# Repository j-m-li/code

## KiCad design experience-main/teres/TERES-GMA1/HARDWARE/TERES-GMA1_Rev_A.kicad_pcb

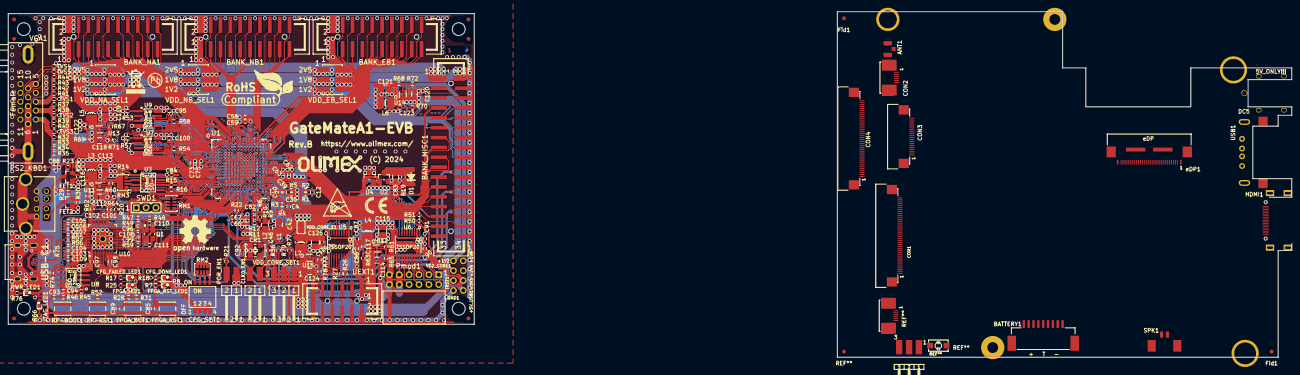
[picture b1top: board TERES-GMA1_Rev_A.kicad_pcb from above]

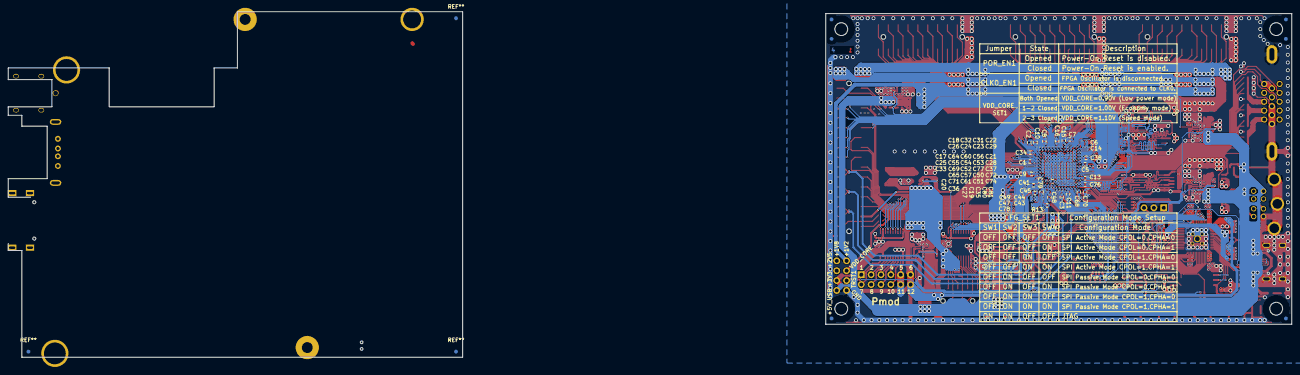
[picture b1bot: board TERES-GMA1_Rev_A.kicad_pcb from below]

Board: 4 copper layers, 120.0 x 80.0 mm, 318 parts (73 on the bottom side), 264 nets.

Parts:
+1V2, +1V8, +2V5, +3V3, +5V_USB1: TESTPAD; TEST_PAD_40x70_Round
ANT1: PCB_WIFI_ANT; U.FL-R-SMT-1
BANK_EB1: B-V-20-LF; GBH-254-SMT-20
BANK_MISC1: B-V-34-LF; GBH-254-SMT-34
BANK_NA1: B-V-20-LF; GBH-254-SMT-20
BANK_NB1: B-V-20-LF; GBH-254-SMT-20
BATTERY1: BATTCON; BATCONN-TERES
C1, C2, C3, C4, C5, C6, C7, C8, C43, C47, C58, C62, C66, C68, C73, C78, C106, C107: 2.2uF/6.3V/20%/X5R/C0402; C_0402_5MIL_DWS
C9, C10, C11, C12, C13, C14, C15, C16, C30, C42, C44, C46, C48, C59, C63, C67, C70, C75, C82, C85, C86, C87, C88, C89, C90, C91, C92, C94, C95, C96, C97, C98, C99, C100, C101, C102, C103, C104, C105, C108, C109: 100nF/10V/20%/X5R/C0402; C_0402_5MIL_DWS
C17, C18, C19, C20, C21, C22, C23, C24, C25, C26, C27, C28, C29, C31, C32, C33, C34, C35, C36, C37, C38, C41, C45, C49, C50, C51, C52, C53, C54, C55, C56, C57, C60, C61, C64, C65, C69, C71, C72, C74, C76, C77, C79, C80, C81: 1nF/50V/10%/X7R/C0402; C_0402_5MIL_DWS
C39, C40, C126: 10uF/6.3V/X5R/20%/C0402; C_0402_5MIL_DWS
C83, C112, C114, C118, C120, C124: 22uF/6.3V/20%/X5R/C0603; C_0603_5MIL_DWS
C84: NA(100nF/10V/20%/X5R/C0402); C_0402_5MIL_DWS
C93: NA/C0402; C_0402_5MIL_DWS
C110, C111: 18pF/50V/5%/C0G/C0402; C_0402_5MIL_DWS
C113, C115, C119, C121, C125: 47uF/6.3V/20%/X5R/C0805; C_0805_5MIL_DWS
C116, C117, C122, C123: NA(2.2uF/6.3V/20%/X5R/C0402); C_0402_5MIL_DWS
CFG_DONE_LED1: LED/GREEN/0603; LED_0603_KA
CFG_FAILED_LED1: LED/RED/0603; LED_0603_KA
CFG_SET1: DSHP04TS-S; DSHP04TS-S-1.27mm_Half_4_Slide
CLK0_EN1: H-WX-1x2-LF(Closed); HN1x2(SMD)_H-WX-1x2-LF
CON1, CON4: CONN_01X40; FPV-WZA21-40-LF
CON2: CONN_01X06; FLEXCON-0.5-6
CON3: CONN_01X20; FPV-WZA21-20-LF
CR1: Q10MHz/30ppm/1.62V-3.63V/4P/5x3.2mm(SX5M10.000M20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; 5032-4P_HCX-3S
D1: 1N5819S4/SOD123; SOD-123_1C-2A_KA
DC5: PWR-JACK-THERES; DC-055-TERES
FET1, FET2: BSS138(SOT-23-3); SOT23
FID1, FID2, FID3, FID7, FID8, FID9: Fiducial; Fiducial1x3
FID4, FID5, FID6, FID10, FID11, FID12: Fiducial; Fiducial1x3_Paste
FPGA_BUT1: YTS-A016-X
FPGA_LED1: LED/GREEN/0603; LED_0603_KA
FPGA_RST1: YTS-A016-X
FPGA_RST_LED1: LED/RED/0603; LED_0603_KA
Fid1, Fid1#2: Fiducial1x3_transp
GND1: TESTPAD; TEST_PAD_40x70_Round
HDMI1: HDMI-SWM-19; HDMI-MINI-TERES
JTAG_LED1: LED/YELLOW/0603; LED_0603_KA
JUMP_CAP1, JUMP_CAP2, JUMP_CAP3, JUMP_CAP4, JUMP_CAP5, JUMP_CAP6: MJ6
L1, L2: FB0805/600R/2A; L_0805_5MIL_DWS
L3, L4, L5, L6, L7: 1.0uH/2.5A/DCR=30mR/20%/3.00x3.00x1.50mm/CD32(SWP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; CD32
Logo_OLIMEX_TB: Logo_OLIMEX_TB
MH1, MH2, MH3, MH4: Mounting_Hole_NPTH; Mounting_Hole_Drill-3.3mm_Clerance-7mm
POR_EN1: H-WX-1x2-LF(Closed); HN1x2(SMD)_H-WX-1x2-LF
PS2_KBD1: MDR6_MINI-DIN; PS2_MDR6_MINI-DIN
PWR_LED1: LED/RED/0603; LED_0603_KA
Pmod1: F-R-2x06-LF; Digilent_Pmod_12-pin
Q1: Q12MHz/20pF/10ppm/4P/3.2x2.5mm; TSX-3.2x2.5mm_GND(3)
R1, R4: NA(200R/1%/R0402); R_0402_5MIL_DWS
R2, R3, R6, R10: 0R/R0402; R_0402_5MIL_DWS
R5: 4.7R/R0402; R_0402_5MIL_DWS
R7, R17, R18, R25, R26, R27, R66, R76: 2.2k/R0402; R_0402_5MIL_DWS
R8, R19, R23, R24, R28, R29, R30, R45, R53, R57: 10k/R0402; R_0402_5MIL_DWS
R9: NA(0R/R0402); R_0402_5MIL_DWS
R11, R12, R13, R15: NA(R0402); R_0402_5MIL_DWS
R14, R16, R21, R49: NA(10k/R0402); R_0402_5MIL_DWS
R20, R36, R46, R50, R51, R59: 100R/R0402; R_0402_5MIL_DWS
R22: 200R/1%/R0402; R_0402_5MIL_DWS
R31, R54, R58: 22R/R0402; R_0402_5MIL_DWS
R32, R37, R41: 430R/1%/R0402; R_0402_5MIL_DWS
R33, R38, R42: 866R/1%/R0402; R_0402_5MIL_DWS
R34, R39, R43: 2.05k/1%/R0402; R_0402_5MIL_DWS
R35, R40, R44: 4.42k/1%/R0402; R_0402_5MIL_DWS
R47, R48: NA(22R/R0402); R_0402_5MIL_DWS
R52: NA(100R/R0402); R_0402_5MIL_DWS
R55, R56: 27R/R0402; R_0402_5MIL_DWS
R60: 3.32k/1%/R0402; R_0402_5MIL_DWS
R61: 4.7k/1%/R0402; R_0402_5MIL_DWS
R62, R63, R69, R70: 100k/R0402; R_0402_5MIL_DWS
R64, R65: 1.05k/1%/R0402; R_0402_5MIL_DWS
R67: 20k/1%/R0402; R_0402_5MIL_DWS
R68, R71, R72: 10k/1%/R0402; R_0402_5MIL_DWS
R73: 1k/1%/R0402; R_0402_5MIL_DWS
R74, R75: 5.1k/1%/R0402; R_0402_5MIL_DWS
R77: 6.04k/1%/R0402; R_0402_5MIL_DWS
R78: 2k/1%/R0402; R_0402_5MIL_DWS
R79: 3.01k/1%/R0402; R_0402_5MIL_DWS
RM1, RM2: RA1206_(4x0603)_4B8_10k; RA1206_(4X0603)_4B8_xx
RM3: NA(RA1206_(4x0603)_4B8_10k); RA1206_(4X0603)_4B8_xx
RP-BOOT1: YTS-A016-X
RP-RST1: YTS-A016-X
SPK1: SPK1; CON-SPK-TERES
SWD1: NA(HN1x3); HN1x3
Sign_Antistatic: Sign_Antistatic
Sign_CE: CE_Sign
Sign_OSHW_8x8: Sign_OSHW_8x8
Sign_PB-Free: Sign_PB-Free
Sign_RecycleBin_1: Sign_RecycleBin_1
Sign_RoHS_1: Sign_RoHS_1
TRST1: TESTPAD; TEST_PAD_40x70_Round
TVS1, TVS2, TVS3, TVS4, TVS5: NA(GG0402052R542P); D_0402_5MIL_DWS
U1: CCGM1A1(FBGA-324); FBGA-324_P0.8mm_Pad0.4mm_Ball0.45mm_Dim15.00x15.00x1.20mm
U2: HX7027(SOT-23-3); SOT-23
U3: NA(ZD25WQ16CSIGT(SOIC-8_208mils)); SO-8_208mil
U4: NA(MCP120T-300I/TT(SOT-23-3)); SOT-23
U5, U6: TXB0108PWR(TSSOP-20); TSSOP20_Pitch-0.65mm_6.6x4.5x1.2mm
U7, U9: LY68S3200SLT(SOIC-8_150mil); SOIC-8_150mil
U8: ZD25WQ16CSIGT(SOIC-8_208mils); SO-8_208mil
U10: RP2040(QFN-56_7x7mm_P0.4mm); QFN56_7x7_Pitch_0.4mm
U11, U12, U13, U14, U15: TPS62A02ADRLR(SOT-563-6); SOT-563-6
UEXT1: P-B-V-10-LF; GBH-254-SMT-10
USB1: USB_A_THERES; USB-A-TERES
USB-C1: USB-C-16P-F(A40-00119-A52-12); USB2.0_TYPE-C(A40-00119-A52-12)_Paste
VDD_CORE1: TESTPAD; TEST_PAD_40x70_Round
VDD_CORE_E1: Closed; SJ_Closed
VDD_CORE_SET1: H-WX-1x3-LF(1-2:Closed/2-3:Opened); HN1x3(SMD)_H-WX-1x3-LF
VDD_EB_SEL1: H-V33X-2x03-LF(1-2:Closed); GPH254SMT02x03(H-V33X-2X3-LF)
VDD_NA_SEL1: H-V33X-2x03-LF(1-2:Closed); GPH254SMT02x03(H-V33X-2X3-LF)
VDD_NB_SEL1: H-V33X-2x03-LF(1-2:Closed); GPH254SMT02x03(H-V33X-2X3-LF)
VGA1: HDR15-3.08-14.5T/VGA15/14.5mm; VGA15-F(HDR15-3.08-14.5T)_DrillSlot
eDP1: LCD_CONN; eDP-TERES

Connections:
+1V2: +1V2.1 (Pad), C121.1, L6.2, R68.2, VDD_EB_SEL1.5, VDD_NA_SEL1.5, VDD_NB_SEL1.5
+1V8: +1V8.1 (Pad), BANK_MISC1.2, C6.1, C14.1, C22.2, C29.2, C38.2, C95.2, C100.2, C119.1, L5.2, R53.1, R57.1, R67.2, U1.A2 (VDD_WC), U1.C2 (VDD_WC), U1.D5 (VDD_WC), U1.F2 (VDD_WC), U1.F5 (VDD_WC), U7.8 (VCC), U9.8 (VCC), VDD_EB_SEL1.3, VDD_NA_SEL1.3, VDD_NB_SEL1.3
+2V5: +2V5.1 (Pad), BANK_MISC1.1, C1.2, C3.2, C4.1, C5.2, C9.1, C11.1, C12.1, C13.1, C17.1, C19.1, C20.2, C21.1, C25.1, C27.1, C28.1, C33.1, C35.1, C36.2, C37.1, C68.1, C70.1, C72.1, C74.1, C76.1, C78.2, C79.1, C80.1, C81.1, C84.2, C87.1, C91.1, C92.2, C94.2, C97.1, C98.1, C99.1, C101.1, C102.1, C103.1, C106.1, C113.1, CFG_FAILED_LED1.2 (A), CFG_SET1.1 (SW1_A), CFG_SET1.2 (SW2_A), CFG_SET1.3 (SW3_A), CFG_SET1.4 (SW4_A), CR1.1 (E/D), CR1.4 (VDD), FET1.1 (G), FET2.1 (G), FPGA_LED1.2 (A), FPGA_RST_LED1.2 (A), L3.2, POR_EN1.1, R2.1, R3.1, R8.2, R11.2, R14.2, R15.2, R24.1, R28.2, R30.1, R45.1, R49.1, R60.2, RM1.1.2, RM1.2.2, RM1.3.2, RM3.1.2, RM3.2.2, RM3.3.2, RM3.4.2, U1.G14 (VDD_EA), U1.H5 (VDD_WB), U1.H17 (VDD_EA), U1.J2 (VDD_WB), U1.J14 (VDD_EA), U1.K5 (VDD_WB), U1.L14 (VDD_EA), U1.L17 (VDD_EA), U1.M2 (VDD_WB), U1.M5 (VDD_WB), U1.N5 (VDD_WA), U1.N11 (VDD_SB), U1.N13 (VDD_SB), U1.P3 (VDD_WA), U1.P5 (VDD_WA), U1.P6 (VDD_SA), U1.P8 (VDD_SA), U1.P10 (VDD_SA), U1.R15 (VDD_SB), U1.T1 (VDD_WA), U1.T14 (VDD_CLK), U1.U3 (VDD_WA), U1.U6 (VDD_SA), U1.U9 (VDD_SA), U3.8 (VCC), U5.2 (Vcca), U5.10 (OE), U6.2 (Vcca), U6.10 (OE), U8.8 (VCC), U10.1 (IOVDD), U10.10 (IOVDD), U10.22 (IOVDD), U10.33 (IOVDD), U10.42 (IOVDD), U10.44 (VREG_VIN), U10.49 (IOVDD), VDD_EB_SEL1.1, VDD_NA_SEL1.1, VDD_NB_SEL1.1
+3V3: +3V3.1 (Pad), C86.1, C90.1, C104.1, C105.1, C115.1, D1.1 (K), L4.2, Pmod1.6, Pmod1.12, R19.1, R26.1, R27.1, R61.2, U4.2 (VDD), U5.19 (Vccb), U6.19 (Vccb), U10.43 (ADC_AVDD), U10.48 (USB_VDD), UEXT1.1
+5V_USB: +5V_USB1.1 (Pad), C88.1, C112.1, C114.1, C118.1, C120.1, C124.1, PS2_KBD1.4, PWR_LED1.2 (A), R23.1, R29.1, R62.2, R63.2, R69.2, R70.2, U11.3 (VIN), U12.3 (VIN), U13.3 (VIN), U14.3 (VIN), U15.3 (VIN), U15.4 (EN), USB-C1.A4 (VBUS), USB-C1.A9 (VBUS), USB-C1.B4 (VBUS), USB-C1.B9 (VBUS)
/+1V1: C107.1, C108.1, C109.1, U10.23 (DVDD), U10.45 (VREG_VOUT), U10.50 (DVDD)
/CFG_DONE: CFG_DONE_LED1.2 (A), U1.V3 (IO_WA_B2/CFG_DONE)
/CFG_MD0: CFG_SET1.5 (SW4_B), RM2.4.1, U1.R5 (CFG_MD0/IO_WA_A0)
/CFG_MD1: CFG_SET1.6 (SW3_B), RM2.3.1, U1.T5 (CFG_MD1/IO_WA_B0)
/CFG_MD2: CFG_SET1.7 (SW2_B), RM2.2.1, U1.U4 (CFG_MD2/IO_WA_A1)
/CFG_MD3: CFG_SET1.8 (SW1_B), RM2.1.1, U1.V4 (CFG_MD3/IO_WA_B1)
/CLK: U8.6 (CLK), U10.52 (QSPI_SCLK(Soft_GPIO))
/CLK0: CLK0_EN1.1, R50.1, U1.N14 (CLK0/IO_SB_A8)
/CLK3: R51.2, U1.R13 (CLK3/IO_SB_A5)
/CSn: C93.2, R45.2, R46.1, U8.1 (#CS), U10.56 (QSPI_SS_N(Soft_GPIO))
/D+: R56.2, U10.47 (USB_DP)
/D-: R55.2, U10.46 (USB_DM)
/EA_A0: U1.M15 (IO_EA_A0), U5.1 (A1)
/EA_A1: U1.L16 (IO_EA_A1), U5.4 (A3)
/EA_A2: U1.K18 (IO_EA_A2), U5.6 (A5)
/EA_A3: U1.K16 (IO_EA_A3), U5.8 (A7)
/EA_A4: U1.J18 (IO_EA_A4), U6.1 (A1)
/EA_A5: U1.J16 (IO_EA_A5), U6.4 (A3)
/EA_A6: U1.H16 (IO_EA_A6), U6.6 (A5)
/EA_A7: U1.G18 (IO_EA_A7), U6.8 (A7)
/EA_A8: BANK_MISC1.5, U1.G16 (IO_EA_A8)
/EA_B0: U1.M14 (IO_EA_B0), U5.3 (A2)
/EA_B1: U1.L15 (IO_EA_B1), U5.5 (A4)
/EA_B2: U1.K17 (IO_EA_B2), U5.7 (A6)
/EA_B3: U1.K15 (IO_EA_B3), U5.9 (A8)
/EA_B4: U1.J17 (IO_EA_B4), U6.3 (A2)
/EA_B5: U1.J15 (IO_EA_B5), U6.5 (A4)
/EA_B6: U1.H15 (IO_EA_B6), U6.7 (A6)
/EA_B7: U1.G17 (IO_EA_B7), U6.9 (A8)
/EA_B8: BANK_MISC1.7, U1.G15 (IO_EA_B8)
/EB_A0: BANK_EB1.19, U1.F18 (IO_EB_A0)
/EB_A1: BANK_EB1.17, U1.F16 (IO_EB_A1)
/EB_A2: BANK_EB1.15, U1.D18 (IO_EB_A2)
/EB_A3: BANK_EB1.13, U1.E16 (IO_EB_A3)
/EB_A4: BANK_EB1.11, U1.C18 (IO_EB_A4)
/EB_A5: BANK_EB1.9, U1.B17 (IO_EB_A5)
/EB_A6: BANK_EB1.7, U1.D16 (IO_EB_A6)
/EB_A7: BANK_EB1.5, U1.D15 (IO_EB_A7)
/EB_A8: BANK_EB1.3, U1.B15 (IO_EB_A8)
/EB_B0: BANK_EB1.20, U1.F17 (IO_EB_B0)
/EB_B1: BANK_EB1.18, U1.F15 (IO_EB_B1)
/EB_B2: BANK_EB1.16, U1.D17 (IO_EB_B2)
/EB_B3: BANK_EB1.14, U1.E15 (IO_EB_B3)
/EB_B4: BANK_EB1.12, U1.C17 (IO_EB_B4)
/EB_B5: BANK_EB1.10, U1.A17 (IO_EB_B5)
/EB_B6: BANK_EB1.8, U1.C16 (IO_EB_B6)
/EB_B7: BANK_EB1.6, U1.C15 (IO_EB_B7)
/EB_B8: BANK_EB1.4, U1.A15 (IO_EB_B8)
/FPGA_BUT: R31.2, U1.P13 (IO_SB_B7)
/FPGA_LED: R25.2, U1.P15 (IO_SB_B6)
/FPGA_RESET_IN: BANK_MISC1.29, C85.2, FPGA_RST1.1, R7.2, R8.1, R20.1, R52.2, U1.T15 (RST_N), U2.1 (VOut), U4.1 (#RST)
/FPGA_SPI_CLK: R15.1, R16.1, U1.N4 (IO_WA_B8/SPI_CLK), U3.6 (CLK)
/FPGA_SPI_CSN: R14.1, U1.N3 (IO_WA_A8/~SPI_CS), U3.1 (#CS)
/FPGA_SPI_D0: RM3.1.1, U1.P2 (IO_WA_B7/SPI_D0), U3.5 (DI(IO0))
/FPGA_SPI_D1: RM3.3.1, U1.P1 (IO_WA_A7/SPI_D1), U3.2 (DO(IO1))
/FPGA_SPI_D2: RM3.2.1, U1.R2 (IO_WA_B6/SPI_D2), U3.3 (#WP(IO2))
/FPGA_SPI_D3: RM3.4.1, U1.R1 (IO_WA_A6/SPI_D3), U3.7 (#HOLD(IO3))
/FPGA_SPI_FWD: BANK_MISC1.3, U1.R4 (IO_WA_B5/SPI_FWD)
/GPIO0: U1.U5 (IO_SA_A0), U10.2 (GPIO0/SPI0_RX/UART0_TX/I2C0_SDA/PWM0_A/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)
/GPIO1: U1.V5 (IO_SA_B0), U10.3 (GPIO1/SPI0_CSn/UART0_RX/I2C0_SCL/PWM0_B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)
/GPIO2: U1.R6 (IO_SA_A1), U10.4 (GPIO2/SPI0_SCK/UART0_CTS/I2C1_SDA/PWM1_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)
/GPIO3: U1.T6 (IO_SA_B1), U10.5 (GPIO3/SPI0_TX/UART0_RTS/I2C1_SCL/PWM1_B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)
/GPIO4: U1.R7 (IO_SA_A2), U10.6 (GPIO4/SPI0_RX/UART1_TX/I2C0_SDA/PWM2_A/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)
/GPIO5: U1.T7 (IO_SA_B2), U10.7 (GPIO5/SPI0_CSn/UART1_RX/I2C0_SCL/PWM2_B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)
/GPIO6: U1.U7 (IO_SA_A3), U10.8 (GPIO6/SPI0_SCK/UART1_CTS/I2C1_SDA/PWM3_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)
/GPIO7: U1.V7 (IO_SA_B3), U10.9 (GPIO7/SPI0_TX/UART1_RTS/I2C1_SCL/PWM3_B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)
/GPIO8: U1.R8 (IO_SA_A4), U10.11 (GPIO8/SPI1_RX/UART1_TX/I2C0_SDA/PWM4_A/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)
/GPIO9: U1.T8 (IO_SA_B4), U10.12 (GPIO9/SPI1_CSn/UART1_RX/I2C0_SCL/PWM4_B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)
/GPIO10: U1.U8 (IO_SA_A5), U10.13 (GPIO10/SPI1_SCK/UART1_CTS/I2C1_SDA/PWM5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)
/GPIO11: U1.V8 (IO_SA_B5), U10.14 (GPIO11/SPI1_TX/UART1_RTS/I2C1_SCL/PWM5_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)
/GPIO12\DBG-UART_TX: U1.R9 (IO_SA_A6), U10.15 (GPIO12/SPI1_RX/UART0_TX/I2C0_SDA/PWM6_A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)
/GPIO13\DBG-UART_RX: U1.T9 (IO_SA_B6), U10.16 (GPIO13/SPI1_CSn/UART0_RX/I2C0_SCL/PWM6_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)
/GPIO14: U1.R10 (IO_SA_A7), U10.17 (GPIO14/SPI1_SCK/UART0_CTS/I2C1_SDA/PWM7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)
/GPIO15: U1.T10 (IO_SA_B7), U10.18 (GPIO15/SPI1_TX/UART0_RTS/I2C1_SCL/PWM7_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)
/GPIO16\JTAG_TDI: RM1.3.1, U1.T2 (JTAG_TDI/IO_WA_A4), U10.27 (GPIO16/SPI0_RX/UART0_TX/I2C0_SDA/PWM0_A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)
/GPIO17\JTAG_TDO: RM1.2.1, U1.U2 (JTAG_TDO/IO_WA_B3), U10.28 (GPIO17/SPI0_CSn/UART0_RX/I2C0_SCL/PWM0_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)
/GPIO18\JTAG_TCK: RM1.4.1, U1.R3 (JTAG_TCK/IO_WA_A5), U10.29 (GPIO18/SPI0_SCK/UART0_CTS/I2C1_SDA/PWM1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)
/GPIO19\JTAG_TMS: RM1.1.1, U1.T3 (JTAG_TMS/IO_WA_B4), U10.30 (GPIO19/SPI0_TX/UART0_RTS/I2C1_SCL/PWM1_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)
/GPIO20\JTAG_RST: R20.2, U10.31 (GPIO20/SPI0_RX/UART1_TX/I2C0_SDA/PWM2_A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)
/GPIO21\JTAG_TRST: TRST1.1 (Pad), U10.32 (GPIO21/SPI0_CSn/UART1_RX/I2C0_SCL/PWM2_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)
/GPIO22\GPIN1: U1.N15 (IO_SB_B8), U10.34 (GPIO22/SPI0_SCK/UART1_CTS/I2C1_SDA/PWM3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)
/GPIO23\CLK1: U1.P12 (CLK1/IO_SB_A7), U10.35 (GPIO23/SPI0_TX/UART1_RTS/I2C1_SCL/PWM3_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)
/GPIO24\CLK2: U1.P14 (CLK2/IO_SB_A6), U10.36 (GPIO24/SPI1_RX/UART1_TX/I2C0_SDA/PWM4_A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)
/GPIO25\JTAG_LED: JTAG_LED1.2 (A), U1.R14 (IO_SB_B5), U10.37 (GPIO25/SPI1_CSn/UART1_RX/I2C0_SCL/PWM4_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)
/GPIO26: U1.R11 (IO_SB_B4), U10.38 (GPIO26/ADC0/SPI1_SCK/UART1_CTS/I2C1_SDA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)
/GPIO27: U1.P11 (IO_SB_A4), U10.39 (GPIO27/ADC1/SPI1_TX/UART1_RTS/I2C1_SCL/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)
/GPIO28: U1.U10 (IO_SA_A8), U10.40 (GPIO28/ADC2/SPI1_RX/UART0_TX/I2C0_SDA/P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)
/GPIO29: U1.V10 (IO_SA_B8), U10.41 (GPIO29/ADC3/SPI1_CSn/UART0_RX/I2C0_SCL/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)
/IO0: U8.5 (DI(IO0)), U10.53 (QSPI_SD0(Soft_GPIO))
/IO1: U8.2 (DO(IO1)), U10.55 (QSPI_SD1(Soft_GPIO))
/IO2: U8.3 (#WP(IO2)), U10.54 (QSPI_SD2(Soft_GPIO))
/IO3: U8.7 (#HOLD(IO3)), U10.51 (QSPI_SD3(Soft_GPIO))
/NA_A0: BANK_NA1.3, U1.A3 (IO_NA_A0)
/NA_A1: BANK_NA1.5, U1.A4 (IO_NA_A1)
/NA_A2: BANK_NA1.7, U1.B5 (IO_NA_A2)
/NA_A3: BANK_NA1.9, U1.C6 (IO_NA_A3)
/NA_A4: BANK_NA1.11, U1.A6 (IO_NA_A4)
/NA_A5: BANK_NA1.13, U1.C7 (IO_NA_A5)
/NA_A6: BANK_NA1.15, U1.C8 (IO_NA_A6)
/NA_A7: BANK_NA1.17, U1.A8 (IO_NA_A7)
/NA_A8: BANK_NA1.19, U1.C9 (IO_NA_A8)
/NA_B0: BANK_NA1.4, U1.B3 (IO_NA_B0)
/NA_B1: BANK_NA1.6, U1.B4 (IO_NA_B1)
/NA_B2: BANK_NA1.8, U1.C5 (IO_NA_B2)
/NA_B3: BANK_NA1.10, U1.D6 (IO_NA_B3)
/NA_B4: BANK_NA1.12, U1.B6 (IO_NA_B4)
/NA_B5: BANK_NA1.14, U1.D7 (IO_NA_B5)
/NA_B6: BANK_NA1.16, U1.D8 (IO_NA_B6)
/NA_B7: BANK_NA1.18, U1.B8 (IO_NA_B7)
/NA_B8: BANK_NA1.20, U1.D9 (IO_NA_B8)
/NB_A0: BANK_NB1.3, U1.B9 (IO_NB_A0)
/NB_A1: BANK_NB1.5, U1.D10 (IO_NB_A1)
/NB_A2: BANK_NB1.7, U1.B11 (IO_NB_A2)
/NB_A3: BANK_NB1.9, U1.D11 (IO_NB_A3)
/NB_A4: BANK_NB1.11, U1.B12 (IO_NB_A4)
/NB_A5: BANK_NB1.13, U1.D12 (IO_NB_A5)
/NB_A6: BANK_NB1.15, U1.D13 (IO_NB_A6)
/NB_A7: BANK_NB1.17, U1.B14 (IO_NB_A7)
/NB_A8: BANK_NB1.19, U1.D14 (IO_NB_A8)
/NB_B0: BANK_NB1.4, U1.A9 (IO_NB_B0)
/NB_B1: BANK_NB1.6, U1.C10 (IO_NB_B1)
/NB_B2: BANK_NB1.8, U1.A11 (IO_NB_B2)
/NB_B3: BANK_NB1.10, U1.C11 (IO_NB_B3)
/NB_B4: BANK_NB1.12, U1.A12 (IO_NB_B4)
/NB_B5: BANK_NB1.14, U1.C12 (IO_NB_B5)
/NB_B6: BANK_NB1.16, U1.C13 (IO_NB_B6)
/NB_B7: BANK_NB1.18, U1.A14 (IO_NB_B7)
/NB_B8: BANK_NB1.20, U1.C14 (IO_NB_B8)
/PG_1V8: C123.1, R70.1, U13.6 (PG), U14.4 (EN)
/PG_2V5: C117.1, R63.1, U11.6 (PG), U12.4 (EN)
/PG_3V3: C122.1, R69.1, U12.6 (PG), U13.4 (EN)
/PG_VCore: C116.1, R62.1, U11.4 (EN), U15.6 (PG)
/POR_EN: POR_EN1.2, R21.2, U1.U1 (POR_EN/IO_WA_A3)
/PS2_CLK: FET2.2 (S), R30.2, U1.N1 (IO_WB_A0)
/PS2_DATA: FET1.2 (S), R24.2, U1.N2 (IO_WB_B0)
/PSRAM_CS#: R53.2, R57.2, U1.E3 (IO_WC_A4), U7.1 (#CS), U9.1 (#CS)
/PSRAM_DATA0: U1.D1 (IO_WC_A5), U7.5 (SI/SIO[0])
/PSRAM_DATA1: U1.D2 (IO_WC_B5), U7.2 (SO/SIO[1])
/PSRAM_DATA2: U1.D3 (IO_WC_A6), U7.3 (SIO[2])
/PSRAM_DATA3: U1.D4 (IO_WC_B6), U7.7 (SIO[3])
/PSRAM_DATA4: U1.C3 (IO_WC_A7), U9.5 (SI/SIO[0])
/PSRAM_DATA5: U1.C4 (IO_WC_B7), U9.2 (SO/SIO[1])
/PSRAM_DATA6: U1.B1 (IO_WC_A8), U9.3 (SIO[2])
/PSRAM_DATA7: U1.B2 (IO_WC_B8), U9.7 (SIO[3])
/PSRAM_SCLK: R54.2, R58.2, U1.E4 (IO_WC_B4)
/RP2040_RST#: C96.1, R49.2, R52.1, RP-RST1.1, U10.26 (RUN(RESET#))
/RP2040_SWCLK: R47.1, U10.24 (SWCLK)
/RP2040_SWDIO: R48.1, U10.25 (SWDIO)
/SB_A0: BANK_MISC1.27, U1.U17 (IO_SB_A0)
/SB_A1: BANK_MISC1.23, U1.R17 (IO_SB_A1)
/SB_A2: BANK_MISC1.19, U1.P17 (IO_SB_A2)
/SB_A3: BANK_MISC1.15, U1.M17 (IO_SB_A3)
/SB_B0: BANK_MISC1.25, U1.U18 (IO_SB_B0)
/SB_B1: BANK_MISC1.21, U1.R18 (IO_SB_B1)
/SB_B2: BANK_MISC1.17, U1.P18 (IO_SB_B2)
/SB_B3: BANK_MISC1.13, U1.M18 (IO_SB_B3)
/SER_CLK_N: BANK_MISC1.20, R13.1, U1.T13 (SER_CLK_N)
/SER_CLK_P: BANK_MISC1.22, R13.2, U1.T12 (SER_CLK)
/SER_RX_N: BANK_MISC1.28, U1.V11 (SER_RX_N)
/SER_RX_P: BANK_MISC1.30, U1.U11 (SER_RX_P)
/SER_TX_N: BANK_MISC1.26, U1.V13 (SER_TX_N)
/SER_TX_P: BANK_MISC1.24, U1.U13 (SER_TX_P)
/UEXT_CS#: U5.12 (B8), UEXT1.10
/UEXT_MISO: U5.15 (B5), UEXT1.7
/UEXT_MOSI: U5.14 (B6), UEXT1.8
/UEXT_RXD: U5.18 (B2), UEXT1.4
/UEXT_SCK: U5.13 (B7), UEXT1.9
/UEXT_SCL: R26.2, U5.17 (B3), UEXT1.5
/UEXT_SDA: R27.2, U5.16 (B4), UEXT1.6
/UEXT_TXD: U5.20 (B1), UEXT1.3
/USB_D+: R56.1, USB-C1.A6 (DP1), USB-C1.B6 (DP2)
/USB_D-: R55.1, USB-C1.A7 (DN1), USB-C1.B7 (DN2)
/VDD_PLL: C39.2, C40.2, C41.2, R5.2, U1.P16 (VDD_PLL)
/VDD_SER: C47.2, C48.2, C49.2, L2.2, R9.1, U1.U12 (VDD_SER), U1.V17 (VDD_SER)
/VDD_SER_PLL: C43.2, C44.2, C45.2, L1.2, U1.T16 (VDD_SER_PLL)
/VGA_Blue_0: R44.2, U1.H2 (IO_WB_B7)
/VGA_Blue_1: R43.2, U1.H1 (IO_WB_A7)
/VGA_Blue_2: R42.2, U1.J4 (IO_WB_B6)
/VGA_Blue_3: R41.2, U1.J3 (IO_WB_A6)
/VGA_Green_0: R40.2, U1.K2 (IO_WB_B5)
/VGA_Green_1: R39.2, U1.K1 (IO_WB_A5)
/VGA_Green_2: R38.2, U1.K4 (IO_WB_B4)
/VGA_Green_3: R37.2, U1.K3 (IO_WB_A4)
/VGA_HSync: TVS5.2 (IO2), U1.M3 (IO_WB_A1), VGA1.13 (HSync)
/VGA_Red_0: R35.2, U1.L2 (IO_WB_B3)
/VGA_Red_1: R34.2, U1.L1 (IO_WB_A3)
/VGA_Red_2: R33.2, U1.L4 (IO_WB_B2)
/VGA_Red_3: R32.2, U1.L3 (IO_WB_A2)
/VGA_VSync: TVS4.2 (IO2), U1.M4 (IO_WB_B1), VGA1.14 (VSync)
/WB_A8: BANK_MISC1.9, U1.H3 (IO_WB_A8)
/WB_B8: BANK_MISC1.11, U1.H4 (IO_WB_B8)
/WC_A0: BANK_MISC1.18, U1.G1 (IO_WC_A0)
/WC_A1: BANK_MISC1.14, U1.G3 (IO_WC_A1)
/WC_A2: BANK_MISC1.10, U1.F3 (IO_WC_A2)
/WC_A3: BANK_MISC1.6, U1.E1 (IO_WC_A3)
/WC_B0: BANK_MISC1.16, U1.G2 (IO_WC_B0)
/WC_B1: BANK_MISC1.12, U1.G4 (IO_WC_B1)
/WC_B2: BANK_MISC1.8, U1.F4 (IO_WC_B2)
/WC_B3: BANK_MISC1.4, U1.E2 (IO_WC_B3)
//CFG_FAILED: R17.2, U1.V2 (IO_WA_A2/~CFG_FAILED)
/~BOOTSEL: R46.2, RP-BOOT1.1
GND: BANK_EB1.2, BANK_MISC1.33, BANK_MISC1.34, BANK_NA1.2, BANK_NB1.2, C1.1, C2.2, C3.1, C4.2, C5.1, C6.2, C7.1, C8.2, C9.2, C10.2, C11.2, C12.2, C13.2, C14.2, C15.2, C16.1, C17.2, C18.1, C19.2, C20.1, C21.2, C22.1, C23.2, C24.1, C25.2, C26.1, C27.2, C28.2, C29.1, C30.2, C31.2, C32.1, C33.2, C34.1, C35.2, C36.1, C37.2, C38.1, C39.1, C40.1, C41.1, C42.2, C43.1, C44.1, C45.1, C46.2, C47.1, C48.1, C49.1, C50.1, C51.1, C52.1, C53.1, C54.1, C55.1, C56.1, C57.1, C58.1, C59.1, C60.1, C61.1, C62.1, C63.1, C64.1, C65.1, C66.1, C67.1, C68.2, C69.1, C70.2, C71.1, C72.2, C73.1, C74.2, C75.1, C76.2, C77.1, C78.1, C79.2, C80.2, C81.2, C82.2, C83.2, C84.1, C85.1, C86.2, C87.2, C88.2, C89.2, C90.2, C91.2, C92.1, C93.1, C94.1, C95.1, C96.2, C97.2, C98.2, C99.2, C100.1, C101.2, C102.2, C103.2, C104.2, C105.2, C106.2, C107.2, C108.2, C109.2, C110.2, C111.2, C112.2, C113.2, C114.2, C115.2, C116.2, C117.2, C118.2, C119.2, C120.2, C121.2, C122.2, C123.2, C124.2, C125.2, C126.1, CR1.2 (VSS), FPGA_BUT1.2, FPGA_RST1.2, GND1.1 (Pad), PS2_KBD1.3, PS2_KBD1.9 (SHIELD1), Pmod1.5, Pmod1.11, Q1.3 (case), R1.1, R4.1, R6.1, R10.1, R12.2, R16.2, R18.2, R21.1, R22.2, R64.2, R65.2, R66.2, R71.2, R72.2, R74.1, R75.1, R76.2, R77.1, R78.2, R79.2, RM1.4.2, RM2.1.2, RM2.2.2, RM2.3.2, RM2.4.2, RP-BOOT1.2, RP-RST1.2, SWD1.2, TVS1.1 (IO1), TVS2.1 (IO1), TVS3.1 (IO1), TVS4.1 (IO1), TVS5.1 (IO1), U1.A1 (GND), U1.A7 (GND), U1.A10 (GND), U1.A13 (GND), U1.A18 (GND), U1.B16 (GND), U1.C1 (GND), U1.E5 (GND), U1.E7 (GND), U1.E9 (GND), U1.E11 (GND), U1.E13 (GND), U1.E18 (GND), U1.F1 (GND), U1.F6 (GND), U1.F8 (GND), U1.F10 (GND), U1.F12 (GND), U1.F14 (GND), U1.G5 (GND), U1.G7 (GND), U1.G9 (GND), U1.G11 (GND), U1.G13 (GND), U1.H6 (GND), U1.H8 (GND), U1.H10 (GND), U1.H12 (GND), U1.H14 (GND), U1.H18 (GND), U1.J1 (GND), U1.J5 (GND), U1.J7 (GND), U1.J9 (GND), U1.J11 (GND), U1.J13 (GND), U1.K6 (GND), U1.K8 (GND), U1.K10 (GND), U1.K12 (GND), U1.K14 (GND), U1.L5 (GND), U1.L7 (GND), U1.L9 (GND), U1.L11 (GND), U1.L13 (GND), U1.L18 (GND), U1.M1 (GND), U1.M6 (GND), U1.M8 (GND), U1.M10 (GND), U1.M12 (GND), U1.M16 (GND), U1.N7 (GND), U1.N9 (GND), U1.N12 (GND), U1.N17 (GND), U1.P4 (GND), U1.P7 (GND), U1.P9 (GND), U1.R12 (GND), U1.R16 (GND), U1.T4 (GND), U1.T11 (GND), U1.T17 (GND), U1.U14 (GND), U1.U15 (GND), U1.V1 (GND), U1.V6 (GND), U1.V9 (GND), U1.V14 (GND), U1.V18 (GND), U2.2 (Vss), U3.4 (GND), U4.3 (GND), U5.11 (GND), U6.11 (GND), U7.4 (GND), U8.4 (GND), U9.4 (GND), U10.19 (TESTEN(GND)), U10.57 (GND(EPAD)), U11.1 (GND), U12.1 (GND), U13.1 (GND), U14.1 (GND), U15.1 (GND), UEXT1.2, USB-C1.0 (SHELL), USB-C1.A1 (GND), USB-C1.A12 (GND), USB-C1.B1 (GND), USB-C1.B12 (GND), VGA1.5 (GND), VGA1.6 (Red_RTN), VGA1.7 (Green_RTN), VGA1.8 (Blue_RTN), VGA1.10 (GND), VGA1.16 (Shield1), VGA1.17 (Shield2)
unnamed: BANK_MISC1.31, R50.2
unnamed: BANK_MISC1.32, R51.1
unnamed: C89.1, FPGA_BUT1.1, R28.1, R31.1
unnamed: C110.1, Q1.1, R59.1
unnamed: CFG_DONE_LED1.1 (K), R18.1
unnamed: CFG_FAILED_LED1.1 (K), R17.1
unnamed: CLK0_EN1.2, R36.1
unnamed: CR1.3 (OUT), R36.2
unnamed: C83.1, D1.2 (A), R19.2, U2.3 (VIn)
unnamed: FET1.3 (D), PS2_KBD1.1, R23.2
unnamed: FET2.3 (D), PS2_KBD1.5, R29.2
unnamed: FPGA_LED1.1 (K), R25.1
unnamed: FPGA_RST_LED1.1 (K), R7.1
unnamed: JTAG_LED1.1 (K), R66.1
unnamed: PWR_LED1.1 (K), R76.1
unnamed: R1.2, R2.2, U1.N18 (VDD_SB)
unnamed: R3.2, R4.2, U1.T18 (VDD_SB)
unnamed: R6.2, U1.U16 (GND)
unnamed: R10.2, U1.V16 (GND)
unnamed: R47.2, SWD1.1
unnamed: R48.2, SWD1.3
unnamed: R77.2, VDD_CORE_SET1.1
unnamed: R79.1, VDD_CORE_SET1.3
unnamed: R41.1, R42.1, R43.1, R44.1, TVS1.2 (IO2), VGA1.3 (Blue)
unnamed: R37.1, R38.1, R39.1, R40.1, TVS2.2 (IO2), VGA1.2 (Green)
unnamed: R32.1, R33.1, R34.1, R35.1, TVS3.2 (IO2), VGA1.1 (Red)
unnamed: R22.1, U1.V12 (SER_RTERM)
unnamed: R9.2, U1.N16 (NC)
unnamed: C82.1, R11.1, R12.1, U1.V15 (POR_ADJ)
unnamed: Pmod1.1, U6.20 (B1)
unnamed: Pmod1.7, U6.18 (B2)
unnamed: Pmod1.2, U6.17 (B3)
unnamed: Pmod1.8, U6.16 (B4)
unnamed: Pmod1.3, U6.15 (B5)
unnamed: Pmod1.9, U6.14 (B6)
unnamed: Pmod1.4, U6.13 (B7)
unnamed: Pmod1.10, U6.12 (B8)
unnamed: R54.1, U7.6 (SCLK)
unnamed: R58.1, U9.6 (SCLK)
unnamed: C111.1, Q1.2, U10.20 (XIN)
unnamed: R59.2, U10.21 (XOUT)
unnamed: R60.1, R64.1, U11.5 (FB)
unnamed: L3.1, U11.2 (SW)
unnamed: R61.1, R65.1, U12.5 (FB)
unnamed: L4.1, U12.2 (SW)
unnamed: R67.1, R71.1, U13.5 (FB)
unnamed: L5.1, U13.2 (SW)
unnamed: R68.1, R72.1, U14.5 (FB)
unnamed: L6.1, U14.2 (SW)
unnamed: R73.1, R78.1, U15.5 (FB), VDD_CORE_SET1.2
unnamed: L7.1, U15.2 (SW)
unnamed: R75.2, USB-C1.A5 (CC1)
unnamed: R74.2, USB-C1.B5 (CC2)
VDD_CORE: C30.1, C42.1, C46.1, C50.2, C51.2, C52.2, C53.2, C54.2, C55.2, C56.2, C57.2, C58.2, C59.2, C60.2, C61.2, C62.2, C63.2, C64.2, C65.2, C66.2, C67.2, C69.2, C71.2, C73.2, C75.2, C77.2, C125.1, C126.2, L1.1, L2.1, L7.2, R5.1, R73.2, U1.F9 (VDD), U1.G6 (VDD), U1.G8 (VDD), U1.G10 (VDD), U1.G12 (VDD), U1.H7 (VDD), U1.H9 (VDD), U1.H11 (VDD), U1.H13 (VDD), U1.J6 (VDD), U1.J8 (VDD), U1.J10 (VDD), U1.J12 (VDD), U1.K7 (VDD), U1.K9 (VDD), U1.K11 (VDD), U1.K13 (VDD), U1.L6 (VDD), U1.L8 (VDD), U1.L10 (VDD), U1.L12 (VDD), U1.M7 (VDD), U1.M9 (VDD), U1.M11 (VDD), U1.M13 (VDD), U1.N6 (VDD), U1.N8 (VDD), U1.N10 (VDD), VDD_CORE1.1 (Pad), VDD_CORE_E1.1, VDD_CORE_E1.2
VDD_EB: BANK_EB1.1, C2.1, C10.1, C18.2, C26.2, C34.2, U1.A16 (VDD_EB), U1.B18 (VDD_EB), U1.E14 (VDD_EB), U1.E17 (VDD_EB), U1.F13 (VDD_EB), VDD_EB_SEL1.2, VDD_EB_SEL1.4, VDD_EB_SEL1.6
VDD_NA: BANK_NA1.1, C7.2, C15.1, C23.1, C31.1, U1.A5 (VDD_NA), U1.B7 (VDD_NA), U1.E6 (VDD_NA), U1.E8 (VDD_NA), U1.F7 (VDD_NA), VDD_NA_SEL1.2, VDD_NA_SEL1.4, VDD_NA_SEL1.6
VDD_NB: BANK_NB1.1, C8.1, C16.2, C24.2, C32.2, U1.B10 (VDD_NB), U1.B13 (VDD_NB), U1.E10 (VDD_NB), U1.E12 (VDD_NB), U1.F11 (VDD_NB), VDD_NB_SEL1.2, VDD_NB_SEL1.4, VDD_NB_SEL1.6

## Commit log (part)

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2025-10-06 Update README with additional information
    Added clarification about release assets.

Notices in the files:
experience-main/teres/TERES-GMA1/HARDWARE/TERES-GMA1_Rev_A.kicad_pcb:
(C) 2024
